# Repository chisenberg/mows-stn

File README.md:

# MOWS
### My Own Weather Station __(station repository)__
This is the MOWS project station code and hardware repository.

### BOM <small> (Build of materials)

| Qty | Item |
|-:|:-|
| 1 | Attiny-85 |
| 5 | 10K resistor |
| 1 | 22K resistor 1% |
| 1 | 47K resistor 1% |
| 1 | 1N5817 diode |
| 1 | STX882 rf 433mhz |
| 1 | MCP1700 3.3v |
| 3 | 2500 Mah NIMH AA|

</small>

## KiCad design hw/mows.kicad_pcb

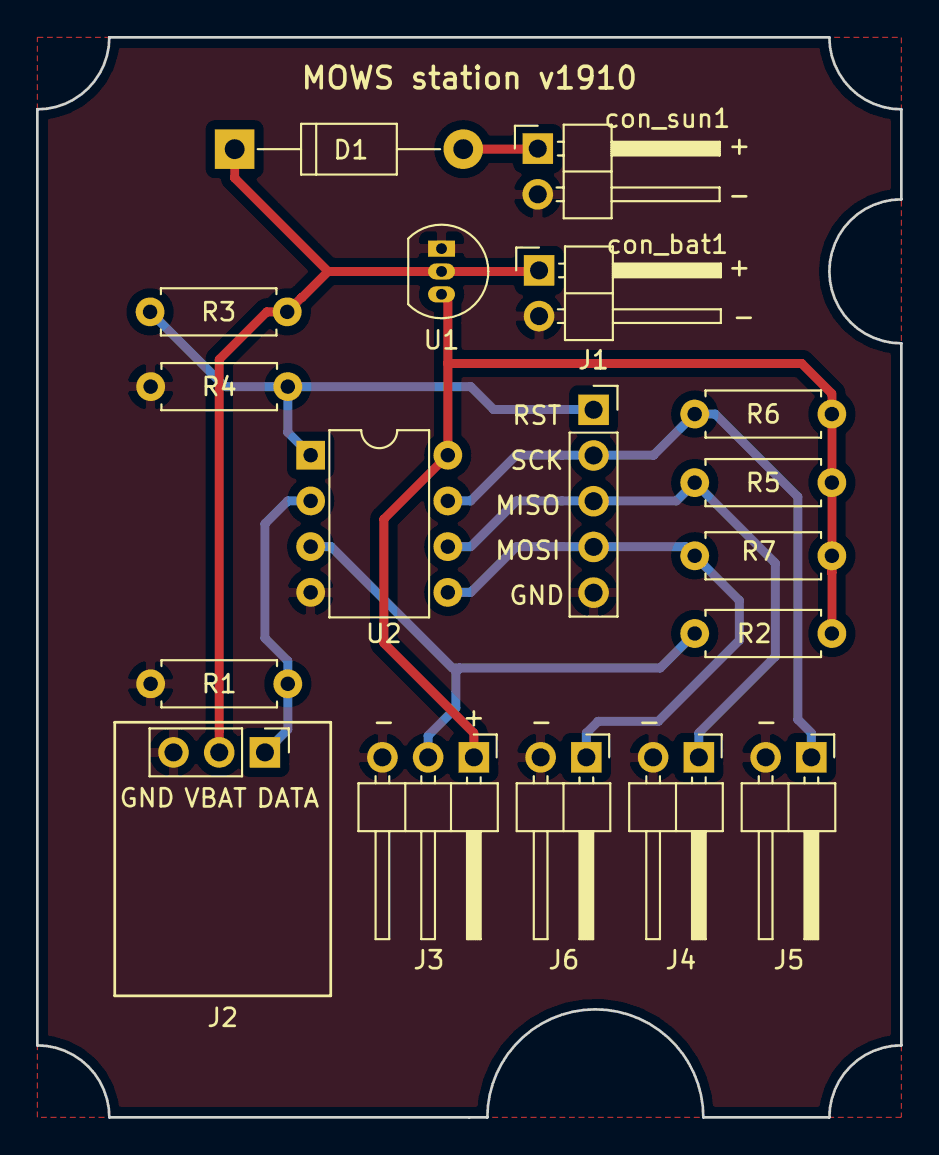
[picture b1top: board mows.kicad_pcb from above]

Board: 2 copper layers, 48.0 x 60.0 mm, 18 parts (0 on the bottom side), 10 nets.

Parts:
D1: D_Schottky; D_DO-41_SOD81_P12.70mm_Horizontal
J1: Conn_01x05; PinSocket_1x05_P2.54mm_Vertical
J2: STX882; Pin_Header_Straight_1x03_Pitch2.54mm
J3: DHT22; PinHeader_1x03_P2.54mm_Horizontal
J4: WSPD; PinHeader_1x02_P2.54mm_Horizontal
J5: WDIR; PinHeader_1x02_P2.54mm_Horizontal
J6: RAIN; PinHeader_1x02_P2.54mm_Horizontal
R1, R2, R5, R6, R7: 10K; R_Axial_DIN0207_L6.3mm_D2.5mm_P7.62mm_Horizontal
R3: 22K; R_Axial_DIN0207_L6.3mm_D2.5mm_P7.62mm_Horizontal
R4: 47K; R_Axial_DIN0207_L6.3mm_D2.5mm_P7.62mm_Horizontal
U1: MCP1700-3302E_TO92; TO-92_Inline_Narrow_Oval
U2: ATTINY85-20PU; DIP-8_W7.62mm
con_bat1: BATT; PinHeader_1x02_P2.54mm_Horizontal
con_sun1: SUN; PinHeader_1x02_P2.54mm_Horizontal

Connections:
+3V3: J3.1, R2.1, R5.1, R6.1, R7.1, U1.3, U2.8
+BATT: D1.1, J2.2, R3.1, U1.2, con_bat1.1
/DHT22: J3.2, R2.2, U2.3
/MISO: J1.3, J4.1, R5.2, U2.6
/MOSI: J1.4, J6.1, R7.2, U2.5
/RFTX: J2.1, R1.1, U2.2
/RST: J1.1, R3.2, R4.1, U2.1
/SCK: J1.2, J5.1, R6.2, U2.7
GND: J1.5, J2.3, J3.3, J4.2, J5.2, J6.2, R1.2, R4.2, U1.1, U2.4, con_bat1.2, con_sun1.2
unnamed: D1.2, con_sun1.1

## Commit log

2018-07-17 New repository for mows station
2018-07-17 Added bom to readme
2018-07-21 Dht22 enabled
2018-08-27 ctimer support for different clocks
2018-09-27 Send end pulse to indicate end
2019-10-24 Nova placa
2019-10-24 Fix missing trace
2019-10-25 pcb labels
2019-11-17 ignore pio build
2020-01-17 Some hardware commits
2020-01-27 Interrupts kind of working
2020-01-28 Tweaks on synk pulse
2020-03-22 Debounce rain
